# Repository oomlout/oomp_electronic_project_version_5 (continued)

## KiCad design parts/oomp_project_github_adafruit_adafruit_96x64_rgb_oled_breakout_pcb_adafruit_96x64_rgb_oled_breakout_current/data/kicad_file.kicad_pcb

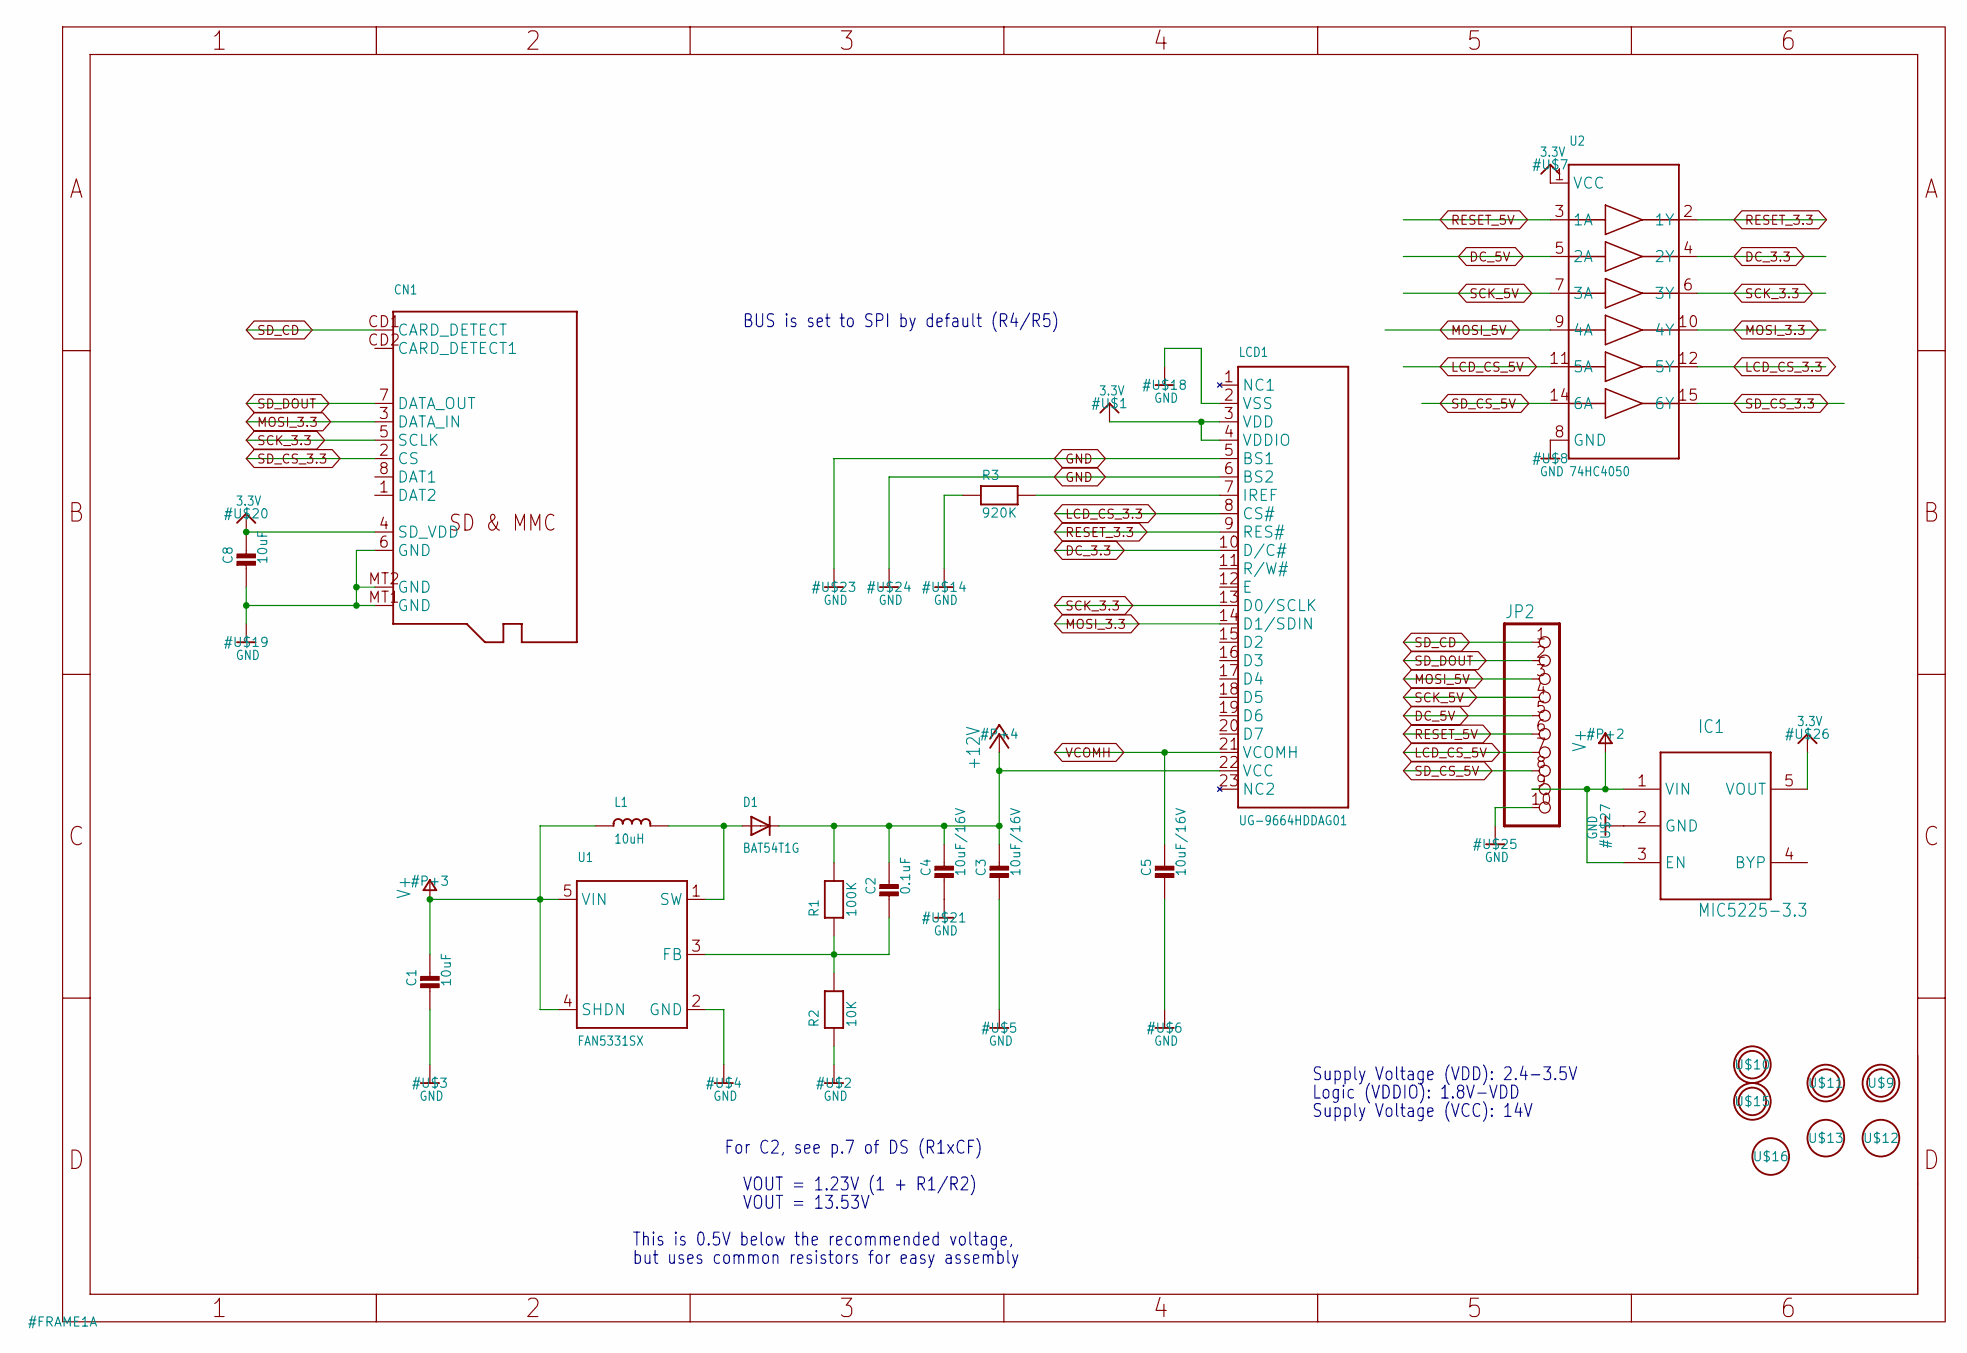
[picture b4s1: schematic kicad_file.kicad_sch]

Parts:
C1, C8: 10uF; 0805
C2: 0.1uF; 0805
C3, C4, C5: 10uF/16V; 0805
CN1: MICROSD
D1: BAT54T1G; SOD-123
IC1: MIC5225-3.3; SOT23-5L
JP2: HEADER-1X10THICKER; 1X10_ROUND_76
L1: 10uH; INDUCTOR_1007
LCD1: UG-9664HDDAG01; UG-9664HDDAG01_WRAPAROUND
R1: 100K; 0805
R2: 10K; 0805
R3: 920K; 0805
U1: FAN5331SX; SOT23-5
U2: 74HC4050; SOIC16
U$9, U$10, U$11, U$15: MOUNTINGHOLE2.5; MOUNTINGHOLE_2.5_PLATED
U$12, U$13, U$16: FIDUCIAL; FIDUCIAL_1MM

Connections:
3.3V: C8.1, CN1.4 (SD_VDD), IC1.5 (VOUT), LCD1.3 (VDD), LCD1.4 (VDDIO), U2.1 (VCC)
+12V: C2.1, C3.1, C4.1, D1.C, LCD1.22 (VCC), R1.2
DC_3.3: LCD1.10 (D/C#), U2.4 (2Y)
DC_5V: JP2.5, U2.5 (2A)
GND: C1.2, C3.2, C4.2, C5.2, C8.2, CN1.6 (GND), CN1.MT1 (GND), CN1.MT2 (GND), IC1.2 (GND), JP2.10, LCD1.2 (VSS), LCD1.5 (BS1), LCD1.6 (BS2), R2.1, R3.1, U1.2 (GND), U2.8 (GND)
LCD_CS_3.3: LCD1.8 (CS#), U2.12 (5Y)
LCD_CS_5V: JP2.7, U2.11 (5A)
MOSI_3.3: CN1.3 (DATA_IN), LCD1.14 (D1/SDIN), U2.10 (4Y)
MOSI_5V: JP2.3, U2.9 (4A)
unnamed: D1.A, L1.P$2 (2), U1.1 (SW)
unnamed: C2.2, R1.1, R2.2, U1.3 (FB)
unnamed: LCD1.7 (IREF), R3.2
RESET_3.3: LCD1.9 (RES#), U2.2 (1Y)
RESET_5V: JP2.6, U2.3 (1A)
SCK_3.3: CN1.5 (SCLK), LCD1.13 (D0/SCLK), U2.6 (3Y)
SCK_5V: JP2.4, U2.7 (3A)
SD_CD: CN1.CD1 (CARD_DETECT), JP2.1
SD_CS_3.3: CN1.2 (CS), U2.15 (6Y)
SD_CS_5V: JP2.8, U2.14 (6A)
SD_DOUT: CN1.7 (DATA_OUT), JP2.2
V+: C1.1, IC1.1 (VIN), IC1.3 (EN), JP2.9, L1.P$1 (1), U1.4 (SHDN), U1.5 (VIN)
VCOMH: C5.1, LCD1.21 (VCOMH)

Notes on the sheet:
Supply Voltage (VCC): 14V
For C2, see p.7 of DS (R1xCF)
BUS is set to SPI by default (R4/R5)
Logic (VDDIO): 1.8V-VDD
Supply Voltage (VDD): 2.4-3.5V
VOUT = 1.23V (1 + R1/R2)
but uses common resistors for easy assembly
VOUT = 13.53V
This is 0.5V below the recommended voltage,

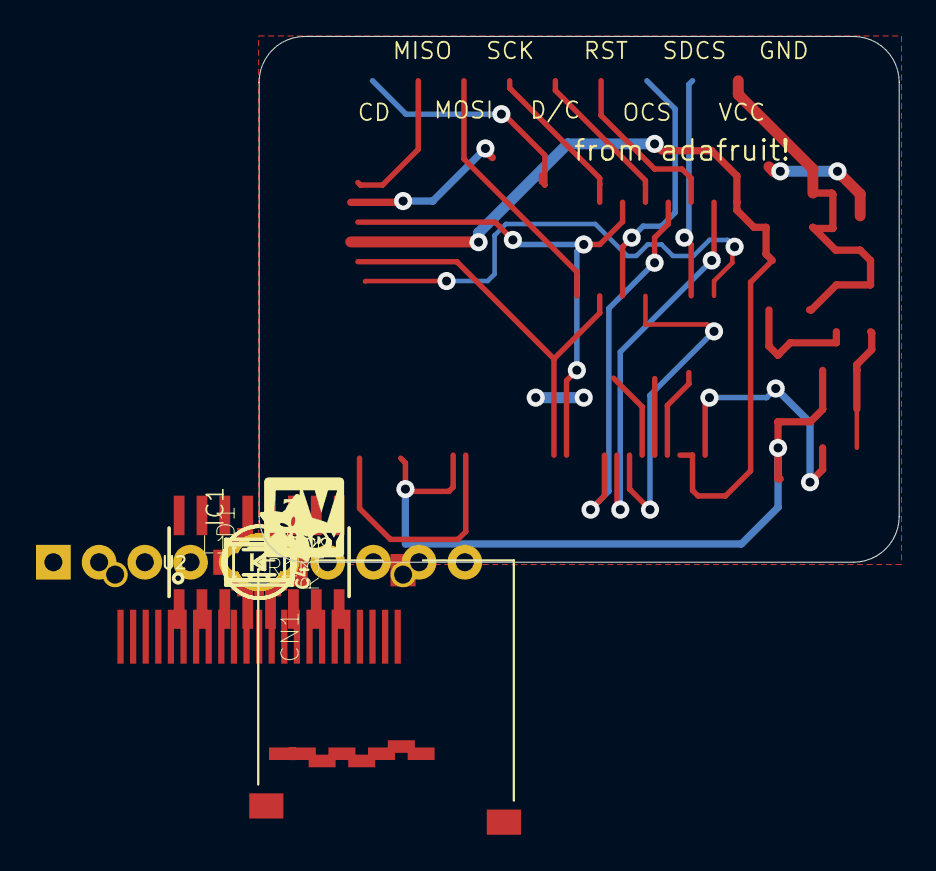
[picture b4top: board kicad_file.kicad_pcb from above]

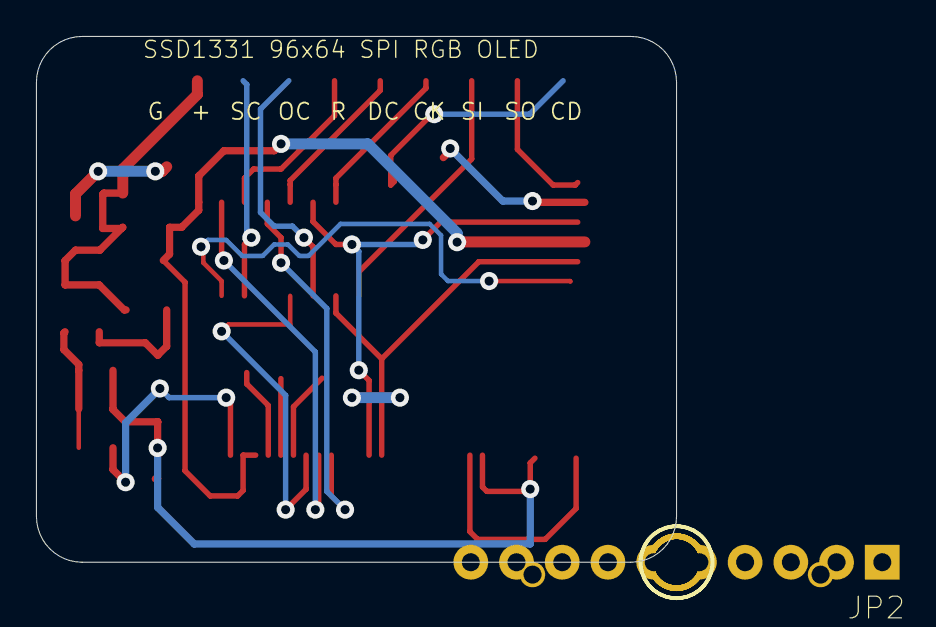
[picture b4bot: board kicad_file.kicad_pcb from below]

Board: 16 copper layers, 35.6 x 29.2 mm, 26 parts (4 on the bottom side), 22 nets.

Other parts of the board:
U$17: ADAFRUIT_3.5MM
U$28: LOGIC_5VREADY_5MM

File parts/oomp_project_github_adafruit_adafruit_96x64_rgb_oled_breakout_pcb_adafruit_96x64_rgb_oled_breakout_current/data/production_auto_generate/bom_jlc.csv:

Comment,Designator,Footprint,LCSC Part #
,JP2,Adafruit 96x64 RGB OLED Breakout v2.0-import-fps:1X10_ROUND_76,C57369
,U$17,Adafruit 96x64 RGB OLED Breakout v2.0-import-fps:ADAFRUIT_3.5MM,
,U$28,Adafruit 96x64 RGB OLED Breakout v2.0-import-fps:LOGIC_5VREADY_5MM,
,CN1,Adafruit 96x64 RGB OLED Breakout v2.0-import-fps:MICROSD,
0.1uF,C2,Adafruit 96x64 RGB OLED Breakout v2.0-import-fps:0805,
100K,R1,Adafruit 96x64 RGB OLED Breakout v2.0-import-fps:0805,C149504
10K,R2,Adafruit 96x64 RGB OLED Breakout v2.0-import-fps:0805,C17414
10uF,"C1,C8",Adafruit 96x64 RGB OLED Breakout v2.0-import-fps:0805,
10uF/16V,"C3,C4,C5",Adafruit 96x64 RGB OLED Breakout v2.0-import-fps:0805,
10uH,L1,Adafruit 96x64 RGB OLED Breakout v2.0-import-fps:INDUCTOR_1007,
74HC4050,U2,Adafruit 96x64 RGB OLED Breakout v2.0-import-fps:SOIC16,
920K,R3,Adafruit 96x64 RGB OLED Breakout v2.0-import-fps:0805,
BAT54T1G,D1,Adafruit 96x64 RGB OLED Breakout v2.0-import-fps:SOD-123,
FAN5331SX,U1,Adafruit 96x64 RGB OLED Breakout v2.0-import-fps:SOT23-5,
FIDUCIAL,"U$12,U$13,U$16",Adafruit 96x64 RGB OLED Breakout v2.0-import-fps:FIDUCIAL_1MM,
MIC5225-3.3,IC1,Adafruit 96x64 RGB OLED Breakout v2.0-import-fps:SOT23-5L,
UG-9664HDDAG01,LCD1,Adafruit 96x64 RGB OLED Breakout v2.0-import-fps:UG-9664HDDAG01_WRAPAROUND,
